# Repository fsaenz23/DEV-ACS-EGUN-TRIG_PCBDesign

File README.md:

# DEV-ACS-EGUN-TRIG_PCBDesign

> The human/operator **front door** (fw-T4.C1.S1.SS4): it orients + routes, and links to deeper resources
> rather than restating them. Agents start at [`AGENTS.md`](AGENTS.md).

## What this is

This repository holds the **printed-circuit-board design of the Trigger Board Assembly** in the Reveam
Accelerator Control System (ACS): a 6-layer Base board and a 4-layer Logic board that plug together and
gate and drive a trigger pulse with isolated status feedback. It is for the engineers who maintain,
review, reorder, or later redesign the boards. It carries the KiCad sources, released Gerbers and reorder
kit, bills of materials, and system documentation, identified independently of any facility the assembly
is later instanced into.

Structural role: `asset-bearing Project`; `project_type`: `product`. asset_id / project_id:
`DEV-ACS-EGUN-TRIG_PCBDesign` (ACS -> EGUN -> TRIG, project-type token `PCBDesign`; cs-T5.C1.S3 /
cs-T5.C1.S17.SS1).

## Scope (fw-T11.C1.S1.SS1)

- **Subject:** the two-board Trigger Board Assembly PCB design (schematics, layouts, BOM, released
  fabrication outputs, system documentation).
- **Axis:** the asset itself -- the PCB design content.
- **Excludes:** firmware or control code (none exists; discrete logic); facility-side instancing
  (E-coded facility repos via `type_ref`); the governance bylaws (FW + CS, consumed as pinned
  submodules); the vendor fiber evaluation boards plugged into J7/J10; the planned all-SMD redesign
  (future, will branch from this baseline); and sibling ACS boards.

This human-prose Scope MUST agree with the machine-readable `scope:` block in
[`compatibility.yaml`](compatibility.yaml) (fw-T11.C1.S1.SS2).

## Status

- **Status:** Phase-2 bootstrap complete (pre-release, `v0.1.0`); the boards themselves are released and in production.
- **Owner:** Francisco Saenz (party `pty-francisco-saenz`; EntraID `fsaenz`). See [`Workflows/ownership/parties.yaml`](Workflows/ownership/parties.yaml).
- **Version:** see [`VERSION`](VERSION) (this repo's own rev). The full multi-module composition cover is the
  document meta-frontpage's job (fw-T8.C1.S11.SS8); this README states this repo's rev and links onward.

## Where things are (routing map)

- [`AGENTS.md`](AGENTS.md) -- **agents start here** (the operating contract + session-start reading order, fw-T7.C1.S1).
- [`BOOTSTRAP.md`](BOOTSTRAP.md) -- the Phase-2 setup steps this repo was scaffolded with.
- [`Definition/`](Definition/) -- the design content: `Drawings/` (KiCad sources + exports), `Fabrication/` (Gerbers, reorder kit), `Equipment/` (BOMs), `Architecture/`, `Calculations/`, `Narratives/`.
- [`Workflows/`](Workflows/) -- the canonical lifecycle scripts (`validate` / `push` / `pull` / `tag` / `deliver`); how to run them: fw-T3.C1.S3 / fw-T3.C1.S9.
- [`Project/STANDING-STATE.md`](Project/STANDING-STATE.md) -- standing state for resuming work (plus optional `Project/dev-tasks/`, fw-T7.C1.S18 / fw-T4.C1.S17).
- [`change-log.md`](change-log.md) + [`minutes/`](minutes/) -- the history of what shipped and why.
- [`docs/`](docs/) -- human documentation (README / FUNCTIONAL / INTERFACES / CHANGES).
- [`Governance/`](Governance/) -- how this repo is governed (the consumed governance submodules + any local governance).

## How to use it

- **Operators:** run the `Workflows/` scripts in order -- `validate.ps1` -> `push.ps1` -> `tag.ps1` (`pull.ps1` to sync, `deliver.ps1` to cut a delivery baseline). Details: fw-T3.C1.S3.
- **Agents:** read `AGENTS.md` first (it routes you to the bylaws + guides).
- **Reordering boards:** start at [`Definition/Fabrication/README.md`](Definition/Fabrication/README.md).

---

*Map, not manual (fw-T4.C1.S1.SS4): this README points to `AGENTS.md`, the bylaws, and the scripts -- it does not restate them (single-source, fw-T11.C1.S2). Keep it current at release (status + version); the routing map is mostly static. `README.md` (humans) and `AGENTS.md` (agents) are the two parallel front doors.*

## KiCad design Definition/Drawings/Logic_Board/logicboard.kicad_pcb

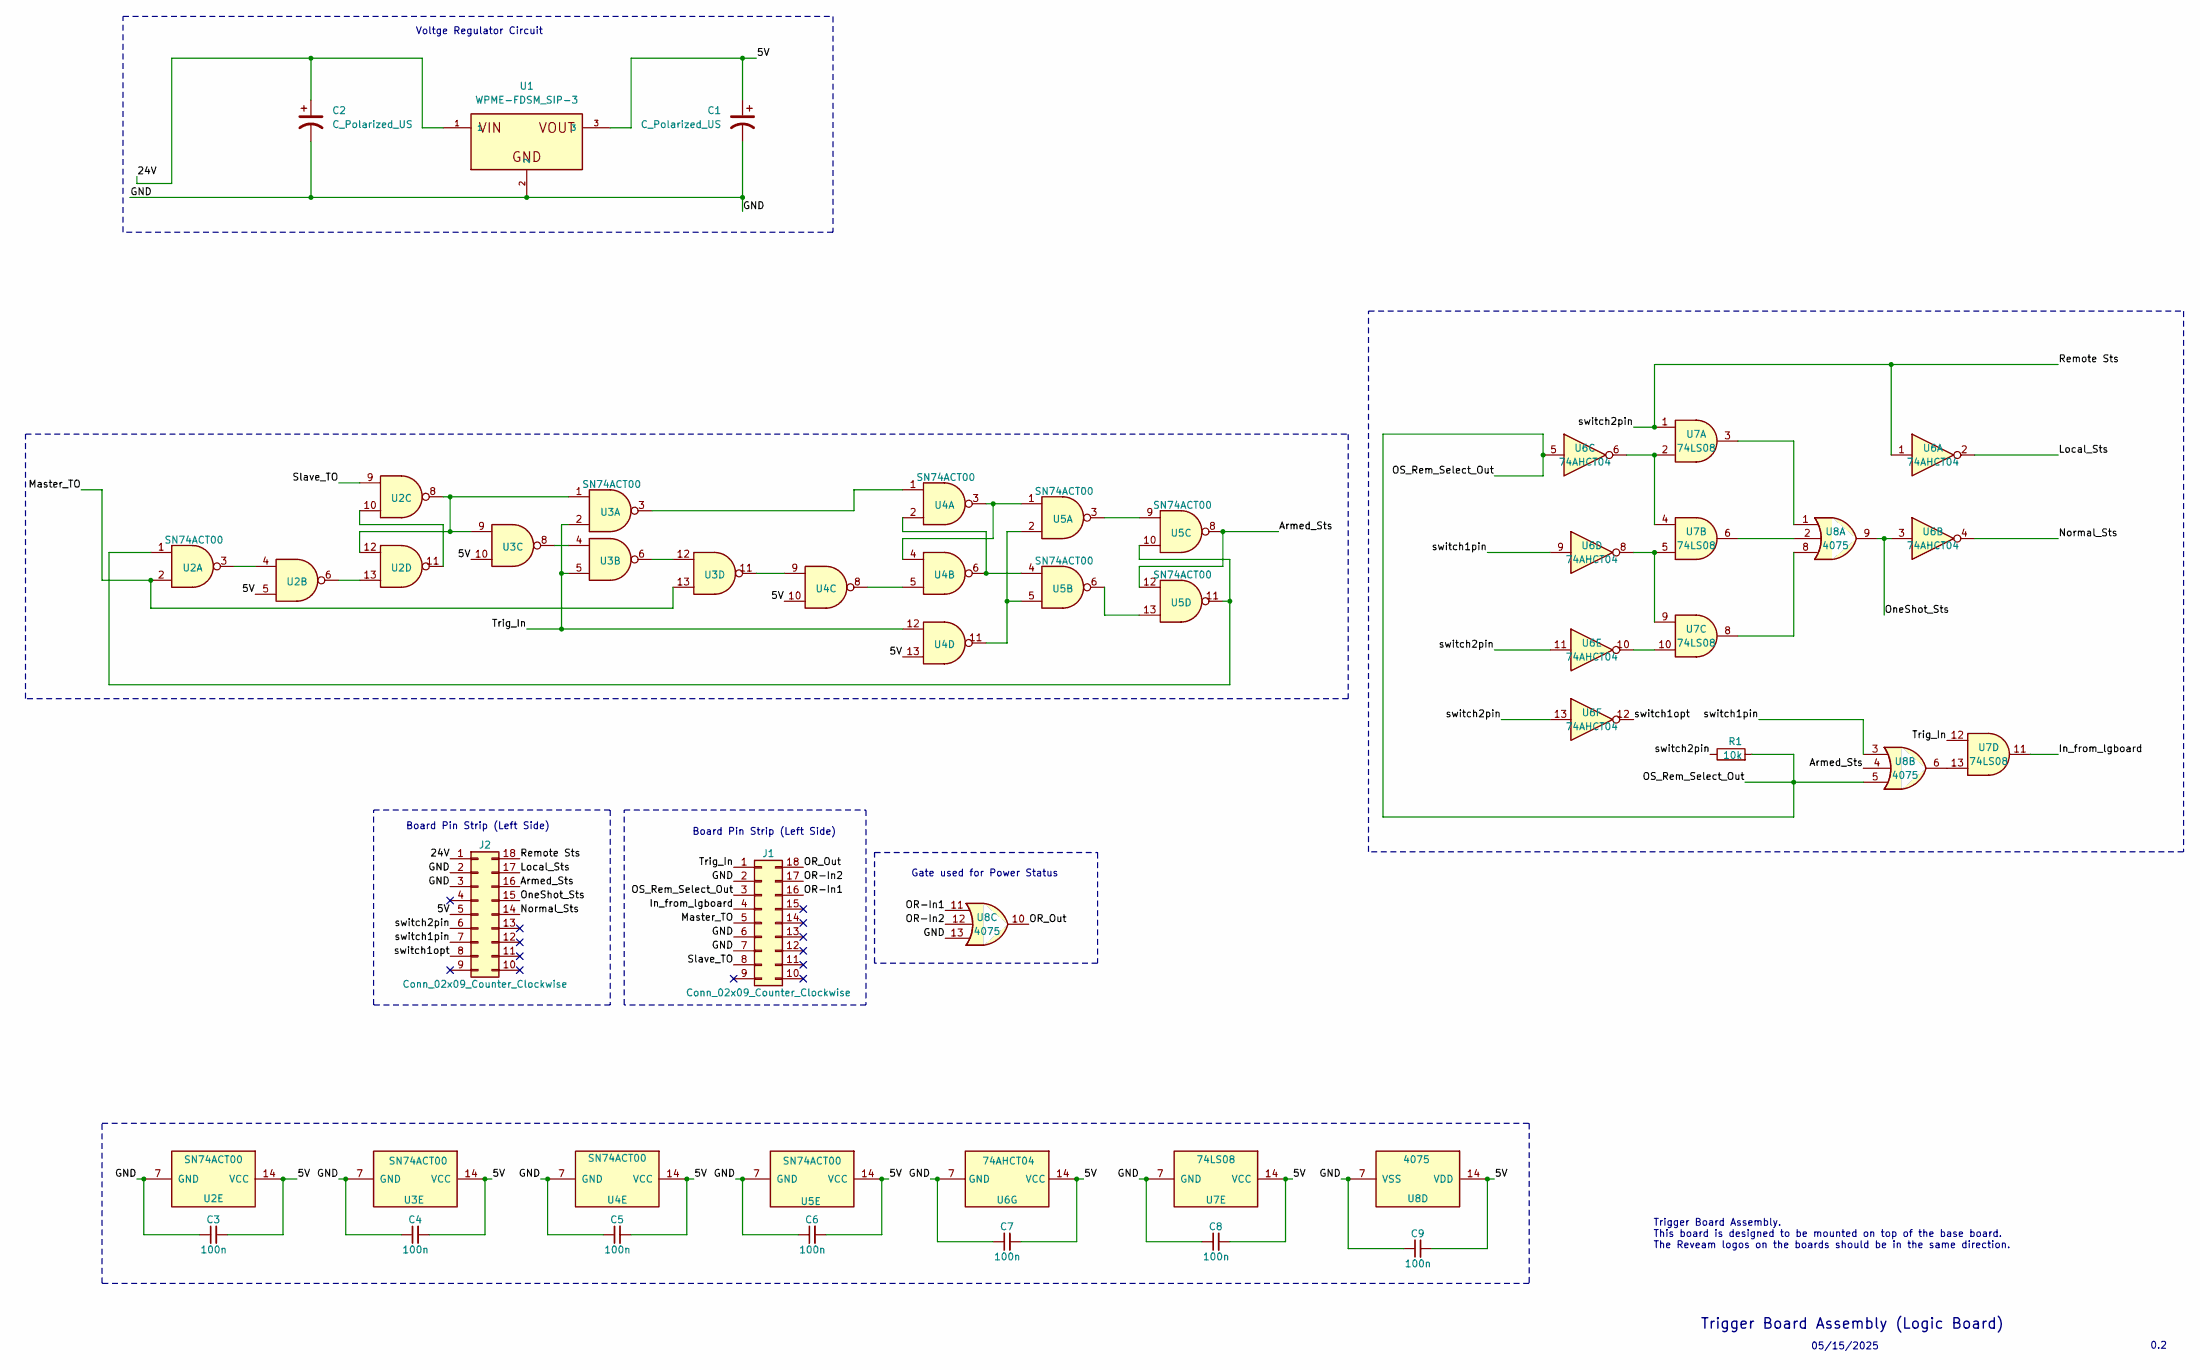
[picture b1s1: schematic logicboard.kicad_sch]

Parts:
C1, C2: C_Polarized_US; CP_Radial_D8.0mm_P3.80mm
C3, C4, C5, C6, C7, C8, C9: 100n; C_Disc_D5.0mm_W2.5mm_P2.50mm
J1, J2: Conn_02x09_Counter_Clockwise; PinHeader_2x09_P2.54mm_Vertical
R1: 10k; R_Axial_DIN0207_L6.3mm_D2.5mm_P10.16mm_Horizontal
U1: WPME-FDSM_SIP-3; CONV_173010578
U2, U3, U4, U5: SN74ACT00; DIP-14_W7.62mm
U6: 74AHCT04; DIP-14_W7.62mm
U7: 74LS08; DIP-14_W7.62mm
U8: 4075; DIP-14_W7.62mm

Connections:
/5V: C1.1, C3.2, C4.2, C5.2, C6.2, C7.2, C8.2, C9.2, J2.5, U1.3, U2.5, U2.14 (VCC), U3.10, U3.14 (VCC), U4.10, U4.13, U4.14 (VCC), U5.14 (VCC), U6.14 (VCC), U7.14 (VCC), U8.14 (VDD)
/24V: C2.1, J2.1, U1.1
/Armed_Sts: J2.16, U5.8, U5.12, U8.4
/GND: C1.2, C2.2, C3.1, C4.1, C5.1, C6.1, C7.1, C8.1, C9.1, J1.2, J1.6, J1.7, J2.2, J2.3, U1.2, U2.7 (GND), U3.7 (GND), U4.7 (GND), U5.7 (GND), U6.7 (GND), U7.7 (GND), U8.7 (VSS), U8.13
/In_from_lgboard: J1.4, U7.11
/Local_Sts: J2.17, U6.2
/Master_TO: J1.5, U2.2, U3.13
/Normal_Sts: J2.14, U6.4
/OR-In1: J1.16, U8.11
/OR-In2: J1.17, U8.12
/OR_Out: J1.18, U8.10
/OS_Rem_Select_Out: J1.3, R1.2, U6.5, U8.5
/OneShot_Sts: J2.15, U6.3, U8.9
/Remote Sts: J2.6, J2.18, R1.1, U6.1, U6.11, U6.13, U7.1
/Slave_TO: J1.8, U2.9
/Trig_In: J1.1, U3.2, U3.5, U4.12, U7.12
/switch1opt: J2.8, U6.12
/switch1pin: J2.7, U6.9, U8.3
unnamed: U2.1, U5.10, U5.11
unnamed: U2.3, U2.4
unnamed: U2.10, U2.11
unnamed: U2.8, U2.12, U3.1, U3.9
unnamed: U2.6, U2.13
unnamed: U3.3, U4.1
unnamed: U3.4, U3.8
unnamed: U3.11, U4.9
unnamed: U3.6, U3.12
unnamed: U4.2, U4.6, U5.4
unnamed: U4.3, U4.4, U5.1
unnamed: U4.5, U4.8
unnamed: U4.11, U5.2, U5.5
unnamed: U5.3, U5.9
unnamed: U5.6, U5.13
unnamed: U6.6, U7.2, U7.4
unnamed: U6.8, U7.5, U7.9
unnamed: U6.10, U7.10
unnamed: U7.3, U8.1
unnamed: U7.6, U8.2
unnamed: U7.8, U8.8
unnamed: U7.13, U8.6

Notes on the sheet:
Voltge Regulator Circuit
Board Pin Strip (Left Side)
05/15/2025
Gate used for Power Status
0.2
Trigger Board Assembly. This board is designed to be mounted on top of the base board. The Reveam logos on the boards should be in the same direction.
Trigger Board Assembly (Logic Board)

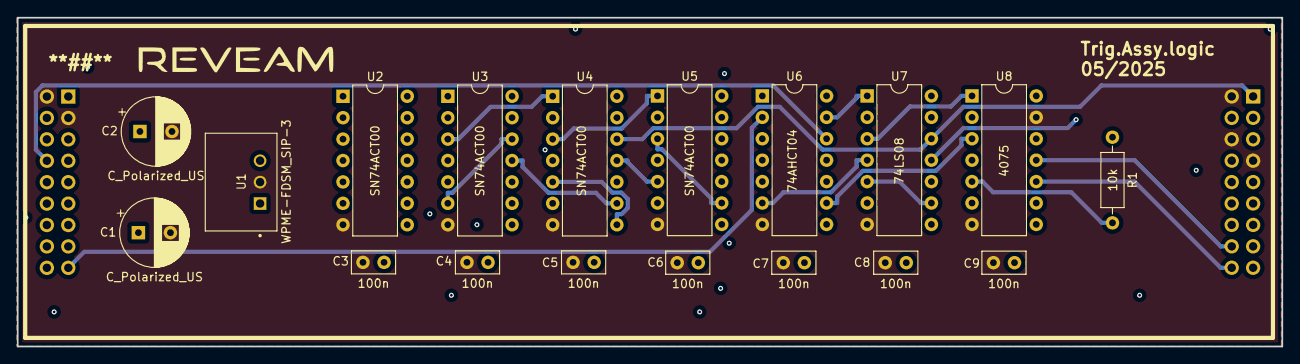
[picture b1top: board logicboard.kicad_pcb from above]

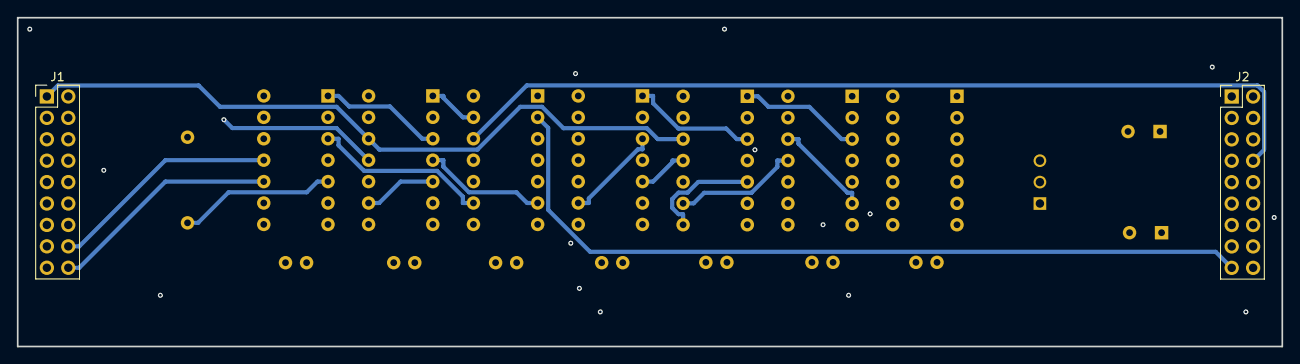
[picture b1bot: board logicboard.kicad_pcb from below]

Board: 4 copper layers, 150.0 x 39.0 mm, 21 parts (2 on the bottom side), 40 nets.

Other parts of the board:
*: LOGO

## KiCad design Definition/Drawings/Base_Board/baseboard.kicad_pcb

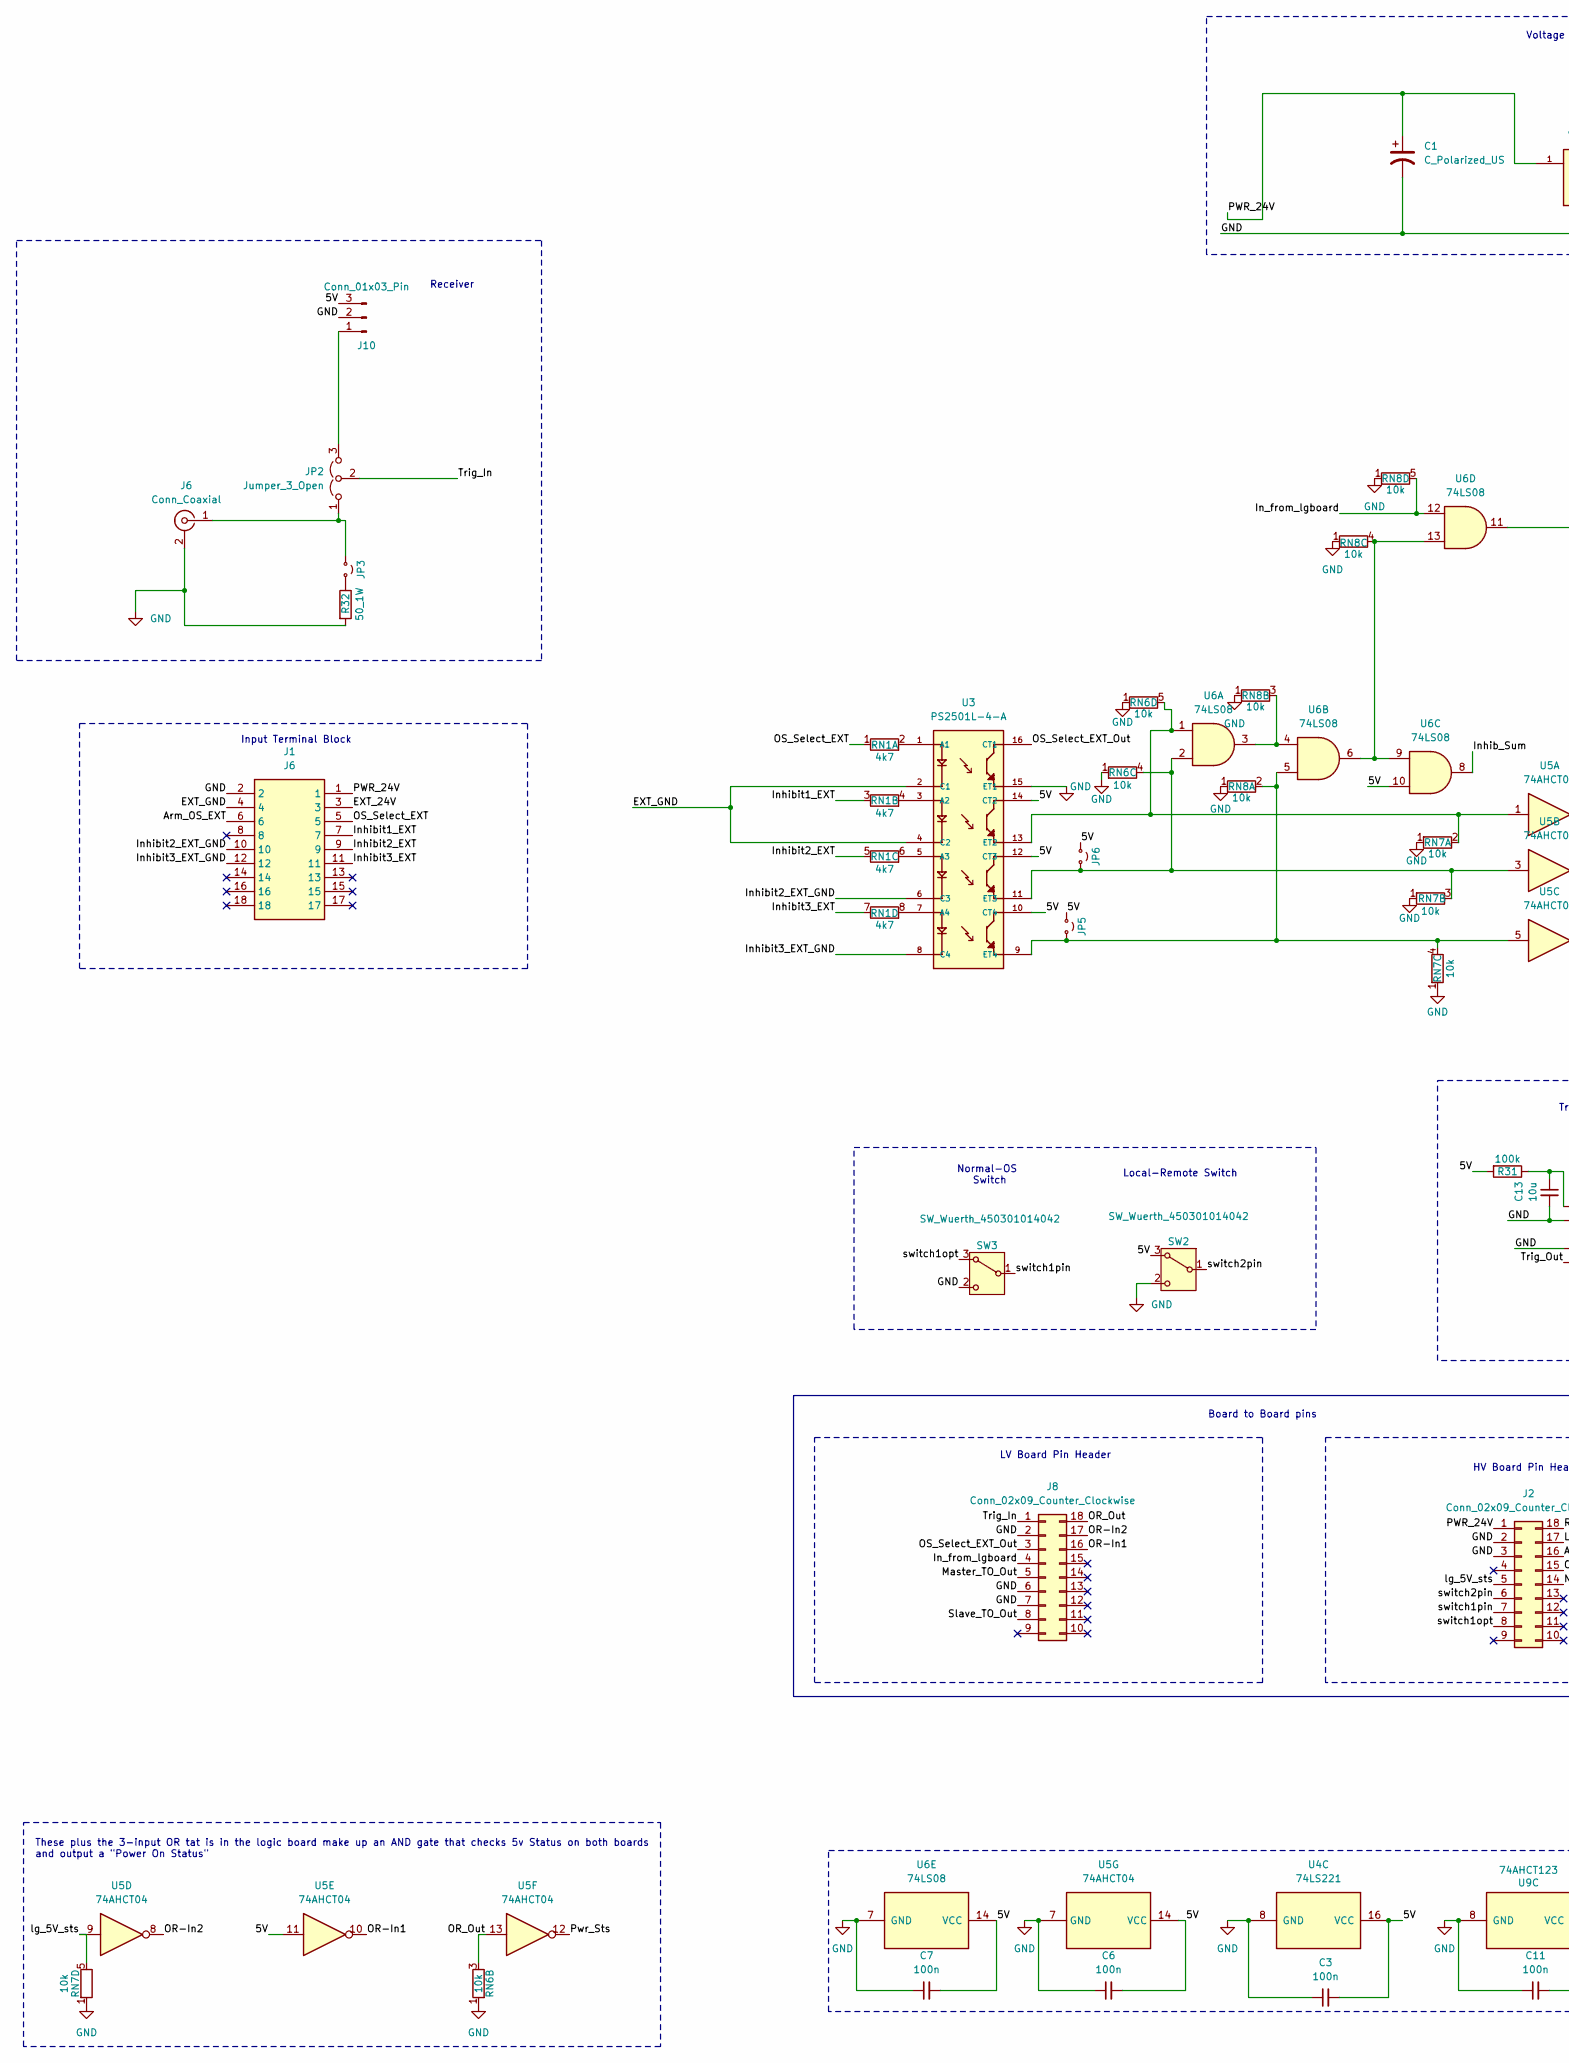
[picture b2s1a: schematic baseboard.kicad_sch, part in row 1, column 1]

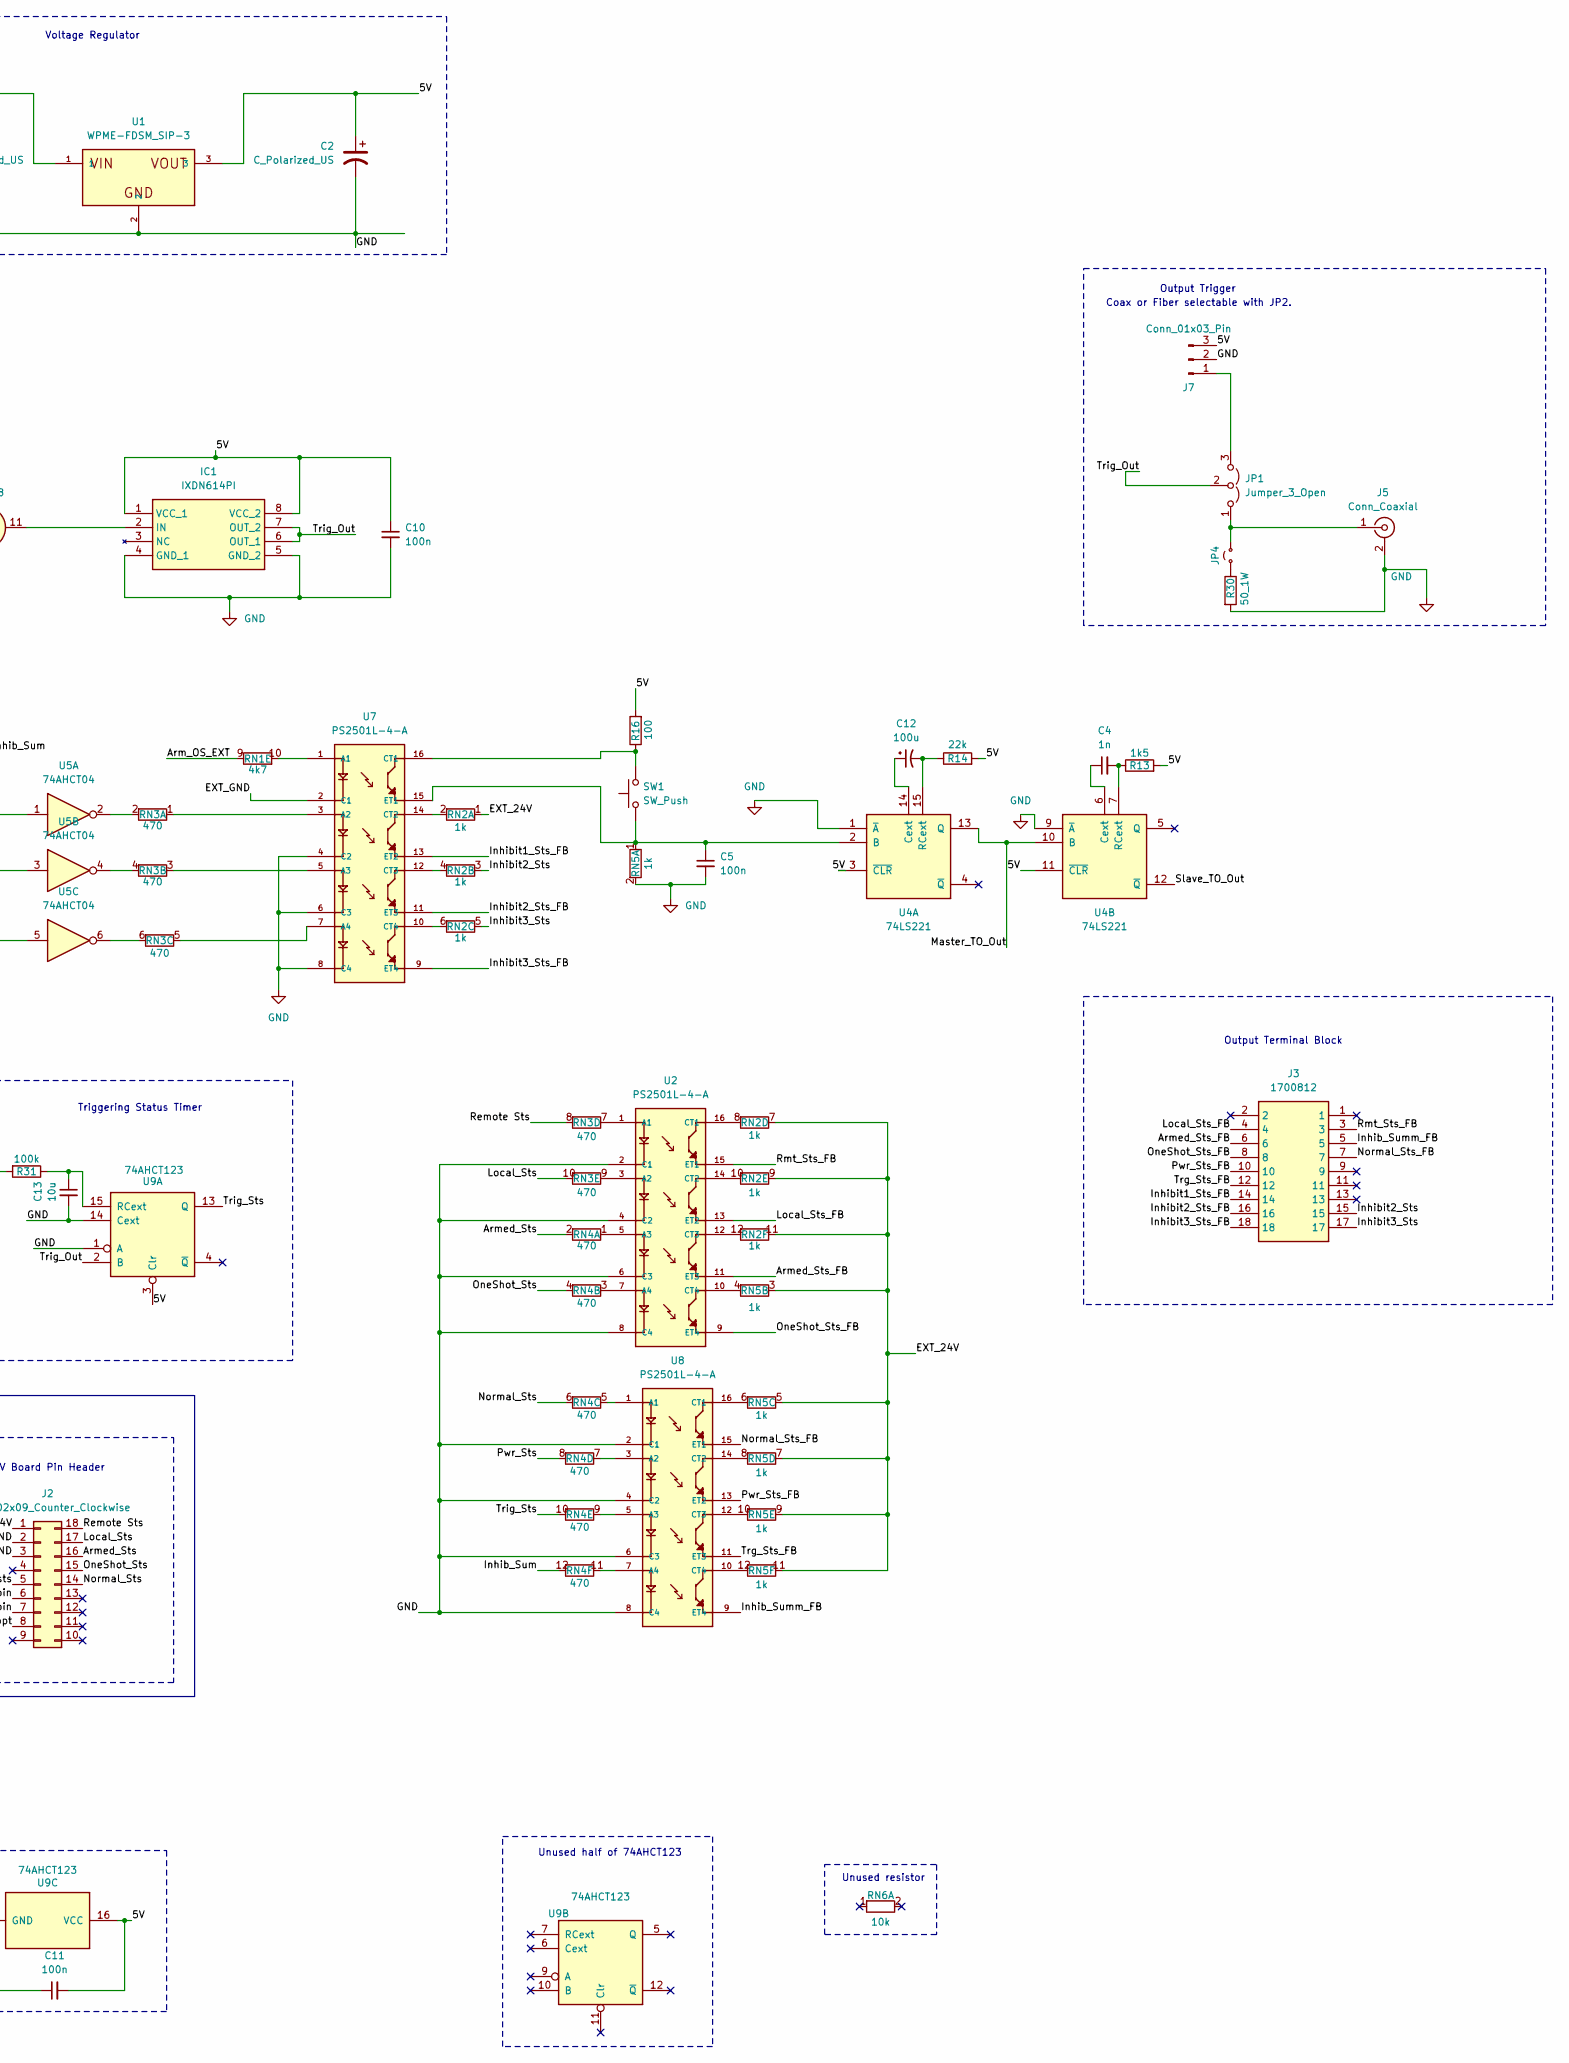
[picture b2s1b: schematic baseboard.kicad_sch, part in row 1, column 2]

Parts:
C1, C2: C_Polarized_US; CP_Radial_D6.3mm_P2.50mm
C3, C5, C6, C7, C10, C11: 100n; C_Disc_D4.7mm_W2.5mm_P5.00mm
C4: 1n; C_Disc_D4.7mm_W2.5mm_P5.00mm
C12: 100u; CP_Radial_D4.0mm_P1.50mm
C13: 10u; C_Disc_D4.7mm_W2.5mm_P5.00mm
IC1: IXDN614PI; DIP-8_W7.62mm; Manufacturer_Part_Number IXDN614PI
J1: J6; 1700812; Manufacturer_Part_Number 1700812
J2, J8: Conn_02x09_Counter_Clockwise; PinSocket_2x09_P2.54mm_Vertical
J3: 1700812; Manufacturer_Part_Number 1700812
J5, J6: Conn_Coaxial; BNC_TEConnectivity_1478204_Vertical
J7, J10: Conn_01x03_Pin; FanPinHeader_1x03_P2.54mm_Vertical
JP1, JP2: Jumper_3_Open; PinHeader_1x03_P2.54mm_Vertical
JP3, JP4, JP5, JP6: Jumper_2_Small_Open; TestPoint_2Pads_Pitch2.54mm_Drill0.8mm
R13: 1k5; R_Axial_DIN0207_L6.3mm_D2.5mm_P10.16mm_Horizontal
R14: 22k; R_Axial_DIN0207_L6.3mm_D2.5mm_P10.16mm_Horizontal
R16: 100; R_Axial_DIN0207_L6.3mm_D2.5mm_P10.16mm_Horizontal
R30, R32: 50_1W; R_Axial_DIN0411_L9.9mm_D3.6mm_P15.24mm_Horizontal
R31: 100k; R_Axial_DIN0207_L6.3mm_D2.5mm_P10.16mm_Horizontal
RN1: 4k7; R_Array_SIP10
RN2, RN5: 1k; R_Array_SIP12
RN3: 470; R_Array_SIP10
RN4: 470; R_Array_SIP12
RN6, RN7, RN8: 10k; R_Array_SIP5
SW1: SW_Push; SW_PUSH_6mm_H5mm
SW2, SW3: SW_Wuerth_450301014042; SW_Slide-03_Wuerth-WS-SLTV_10x2.5x6.4_P2.54mm
U1: WPME-FDSM_SIP-3; CONV_173010578
U2, U3, U7, U8: PS2501L-4-A; DIP-16_W7.62mm
U4: 74LS221; DIP-16_W7.62mm
U5: 74AHCT04; DIP-14_W7.62mm
U6: 74LS08; DIP-14_W7.62mm
U9: 74AHCT123; DIP-16_W7.62mm

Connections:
/5V: C2.1, C3.2, C6.2, C7.2, C10.1, C11.2, IC1.1 (VCC_1), IC1.8 (VCC_2), J7.3, J10.3, JP5.1 (A), JP6.1 (A), R13.2, R14.2, R16.2, R31.2, SW2.3 (A), U1.3, U3.10 (CT4), U3.12 (CT3), U3.14 (CT2), U4.3 (~CLR), U4.11 (~CLR), U4.16 (VCC), U5.11, U5.14 (VCC), U6.10, U6.14 (VCC), U9.3 (Clr), U9.16 (VCC)
/Arm_OS_EXT: J1.6, RN1.9 (R5.1)
/Armed_Sts: J2.16, RN4.2 (R1.2)
/Armed_Sts_FB: J3.6, U2.11 (ET3)
/EXT_24V: J1.3, RN2.1 (R1.1), RN2.7 (R4.1), RN2.9 (R5.1), RN2.11 (R6.1), RN5.3 (R2.1), RN5.5 (R3.1), RN5.7 (R4.1), RN5.9 (R5.1), RN5.11 (R6.1)
/EXT_GND: J1.4, U3.2 (C1), U3.4 (C2), U7.2 (C1)
/In_from_lgboard: J8.4, RN8.5 (R4.2), U6.12
/Inhib_Sum: RN4.12 (R6.2), U6.8
/Inhib_Summ_FB: J3.5, U8.9 (ET4)
/Inhibit1_EXT: J1.7, RN1.3 (R2.1)
/Inhibit1_Sts_FB: J3.14, U7.13 (ET2)
/Inhibit2_EXT: J1.9, RN1.5 (R3.1)
/Inhibit2_EXT_GND: J1.10, U3.6 (C3)
/Inhibit2_Sts: J3.15, RN2.3 (R2.1)
/Inhibit2_Sts_FB: J3.16, U7.11 (ET3)
/Inhibit3_EXT: J1.11, RN1.7 (R4.1)
/Inhibit3_EXT_GND: J1.12, U3.8 (C4)
/Inhibit3_Sts: J3.17, RN2.5 (R3.1)
/Inhibit3_Sts_FB: J3.18, U7.9 (ET4)
/Local_Sts: J2.17, RN3.10 (R5.2)
/Local_Sts_FB: J3.4, U2.13 (ET2)
/Master_TO_Out: J8.5, U4.10 (B), U4.13 (Q)
/Normal_Sts: J2.14, RN4.6 (R3.2)
/Normal_Sts_FB: J3.7, U8.15 (ET1)
/OR-In1: J8.16, U5.10
/OR-In2: J8.17, U5.8
/OR_Out: J8.18, RN6.3 (R2.2), U5.13
/OS_Select_EXT: J1.5, RN1.1 (R1.1)
/OS_Select_EXT_Out: J8.3, U3.16 (CT1)
/OneShot_Sts: J2.15, RN4.4 (R2.2)
/OneShot_Sts_FB: J3.8, U2.9 (ET4)
/PWR_24V: C1.1, J1.1, J2.1, U1.1
/Pwr_Sts: RN4.8 (R4.2), U5.12
/Pwr_Sts_FB: J3.10, U8.13 (ET2)
/Remote Sts: J2.18, RN3.8 (R4.2)
/Rmt_Sts_FB: J3.3, U2.15 (ET1)
/Slave_TO_Out: J8.8, U4.12 (~Q)
/Trg_Sts_FB: J3.12, U8.11 (ET3)
/Trig_In: J8.1, JP2.2 (C)
/Trig_Out: IC1.6 (OUT_1), IC1.7 (OUT_2), JP1.2 (C), U9.2 (B)
/Trig_Sts: RN4.10 (R5.2), U9.13 (Q)
/lg_5V_sts: J2.5, RN7.5 (R4.2), U5.9
/switch1opt: J2.8, SW3.3 (A)
/switch1pin: J2.7, SW3.1 (B)
/switch2pin: J2.6, SW2.1 (B)
GND: C1.2, C2.2, C3.1, C5.2, C6.1, C7.1, C10.2, C11.1, C13.2, IC1.4 (GND_1), IC1.5 (GND_2), J1.2, J2.2, J2.3, J5.2 (Ext), J6.2 (Ext), J7.2, J8.2, J8.6, J8.7, J10.2, R30.2, R32.2, RN5.2 (R1.2), RN6.1 (R1), RN7.1 (R1), RN8.1 (R1), SW2.2 (C), SW3.2 (C), U1.2, U2.2 (C1), U2.4 (C2), U2.6 (C3), U2.8 (C4), U3.15 (ET1), U4.1 (~A), U4.8 (GND), U4.9 (~A), U5.7 (GND), U6.7 (GND), U7.4 (C2), U7.6 (C3), U7.8 (C4), U8.2 (C1), U8.4 (C2), U8.6 (C3), U8.8 (C4), U9.1 (A), U9.8 (GND), U9.14 (Cext)
unnamed: IC1.2 (IN), U6.11
unnamed: J5.1 (In), JP1.1 (A), JP4.2 (B)
unnamed: J6.1 (In), JP2.1 (A), JP3.1 (A)
unnamed: J7.1, JP1.3 (B)
unnamed: J10.1, JP2.3 (B)
unnamed: JP3.2 (B), R32.1
unnamed: JP4.1 (A), R30.1
unnamed: JP5.2 (B), RN7.4 (R3.2), RN8.2 (R1.2), U3.9 (ET4), U5.5, U6.5
unnamed: JP6.2 (B), RN6.4 (R3.2), RN7.3 (R2.2), U3.11 (ET3), U5.3, U6.2
unnamed: RN1.2 (R1.2), U3.1 (A1)
unnamed: RN1.4 (R2.2), U3.3 (A2)
unnamed: RN1.6 (R3.2), U3.5 (A3)
unnamed: RN1.8 (R4.2), U3.7 (A4)
unnamed: RN1.10 (R5.2), U7.1 (A1)
unnamed: RN2.2 (R1.2), U7.14 (CT2)
unnamed: RN2.4 (R2.2), U7.12 (CT3)
unnamed: RN2.6 (R3.2), U7.10 (CT4)
unnamed: RN2.8 (R4.2), U2.16 (CT1)
unnamed: RN2.10 (R5.2), U2.14 (CT2)
unnamed: RN2.12 (R6.2), U2.12 (CT3)
unnamed: RN3.1 (R1.1), U7.3 (A2)
unnamed: RN3.2 (R1.2), U5.2
unnamed: RN3.3 (R2.1), U7.5 (A3)
unnamed: RN3.4 (R2.2), U5.4
unnamed: RN3.5 (R3.1), U7.7 (A4)
unnamed: RN3.6 (R3.2), U5.6
unnamed: RN3.7 (R4.1), U2.1 (A1)
unnamed: RN3.9 (R5.1), U2.3 (A2)
unnamed: RN4.1 (R1.1), U2.5 (A3)
unnamed: RN4.3 (R2.1), U2.7 (A4)
unnamed: RN4.5 (R3.1), U8.1 (A1)
unnamed: RN4.7 (R4.1), U8.3 (A2)
unnamed: RN4.9 (R5.1), U8.5 (A3)
unnamed: RN4.11 (R6.1), U8.7 (A4)
unnamed: C5.1, RN5.1 (R1.1), SW1.1, U4.2 (B), U7.15 (ET1)
unnamed: RN5.4 (R2.2), U2.10 (CT4)
unnamed: RN5.6 (R3.2), U8.16 (CT1)
unnamed: RN5.8 (R4.2), U8.14 (CT2)
unnamed: RN5.10 (R5.2), U8.12 (CT3)
unnamed: RN5.12 (R6.2), U8.10 (CT4)
unnamed: RN6.5 (R4.2), RN7.2 (R1.2), U3.13 (ET2), U5.1, U6.1
unnamed: RN8.3 (R2.2), U6.3, U6.4
unnamed: RN8.4 (R3.2), U6.6, U6.9, U6.13
unnamed: C12.1, U4.14 (Cext)
unnamed: C12.2, R14.1, U4.15 (RCext)
unnamed: C4.1, U4.6 (Cext)
unnamed: C4.2, R13.1, U4.7 (RCext)
unnamed: R16.1, SW1.2, U7.16 (CT1)
unnamed: C13.1, R31.1, U9.15 (RCext)

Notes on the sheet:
Triggering Status Timer
Voltage Regulator
Output Trigger
These plus the 3-input OR tat is in the logic board make up an AND gate that checks 5v Status on both boards and output a "Power On Status"
HV Board Pin Header
Receiver
Coax or Fiber selectable with JP2.
Local-Remote Switch
Normal-OS Switch
LV Board Pin Header
Board to Board pins
Unused resistor
Output Terminal Block
Unused half of 74AHCT123
Input Terminal Block

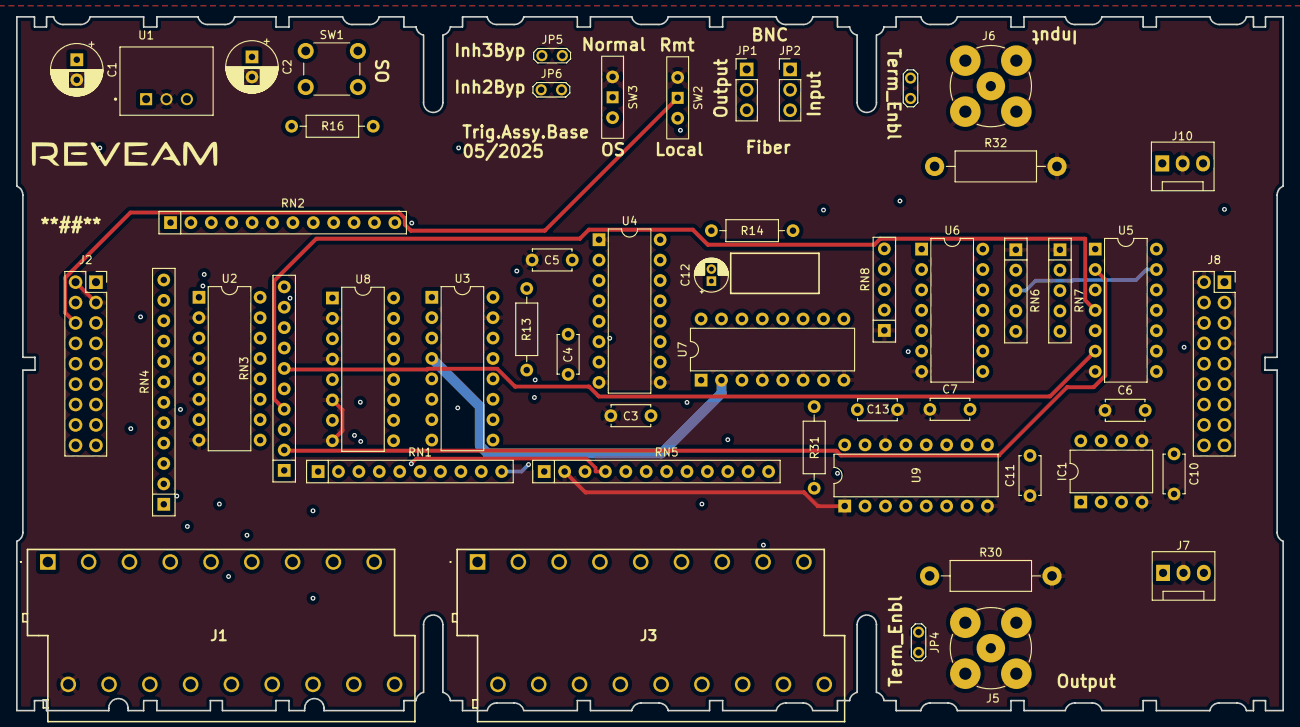
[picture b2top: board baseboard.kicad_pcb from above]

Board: 6 copper layers, 157.7 x 86.4 mm, 53 parts (0 on the bottom side), 95 nets.

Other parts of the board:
*: LOGO
